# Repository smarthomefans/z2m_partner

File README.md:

# [中文文档](https://bbs.iobroker.cn/t/topic/882)

# z2m hardware module

This is hardware module for [iobroker.zigbee](https://github.com/ioBroker/ioBroker.zigbee) and [zigbee2mqtt](https://github.com/Koenkk/zigbee2mqtt) or [Zigbee to Tasmota](https://github.com/arendst/Tasmota/wiki/Zigbee).  
If you can speak Chinese and be interested with this project, please look at this [post](https://bbs.iobroker.cn/t/topic/882/33) in [ioBroker China BBS](https://bbs.iobroker.cn/)

## **V2P1 version is ready to ship**

## What's the difference

- Use [E18-MS1PA1-IPX](http://www.ebyte.com/en/product-view-news.aspx?id=123) zigbee module. 20dBm power can make sure zigbee net work signal is strong.
- Add an ESP8266 module. Give you another option that can connect zigbee module though wifi-to-serial (I was using this [project](https://github.com/smarthomefans/ESP32-Serial-Bridge)).
If your machine running smarthome platform, such as ioBroker or homeassistant, is put in a hidden corner, for better signal coverage, you can put your zigbee module in some where else.
- ESP8266 connected to E18 firmware download pins, give you a chance that can update E18 though ESP8266, no need to use CC-DEBUG.
- There will be 4 options for different TTY connection:
  - USB TTY <==> ESP 8266 TTY. This option is used for download firmware for E18.
  - USB TTY <==> E18 TTY. If you can connect your module though USB wire, this is more stable.
  - USB TTY <==> ESP 8266 debug port. ESP 8266 TTY <==> E18 TTY. Connect though wifi, and you can capture debug infomation though USB TTY.
  - ESP 8266 TTY <==> E18 TTY. Connect though TTY.

## Hardware module images

## 3D cover

## [SCH](https://github.com/smarthomefans/z2m_partner/raw/master/project/z2m_partner.pdf) preview

## PCB preview

## BOM list
[BOM](https://github.com/smarthomefans/z2m_partner/blob/master/documents/bom.md) can get from here.

## Thanks to

- [modkam](https://modkam.ru/), [kirovilya](https://github.com/kirovilya), [Koenkk](https://github.com/Koenkk).

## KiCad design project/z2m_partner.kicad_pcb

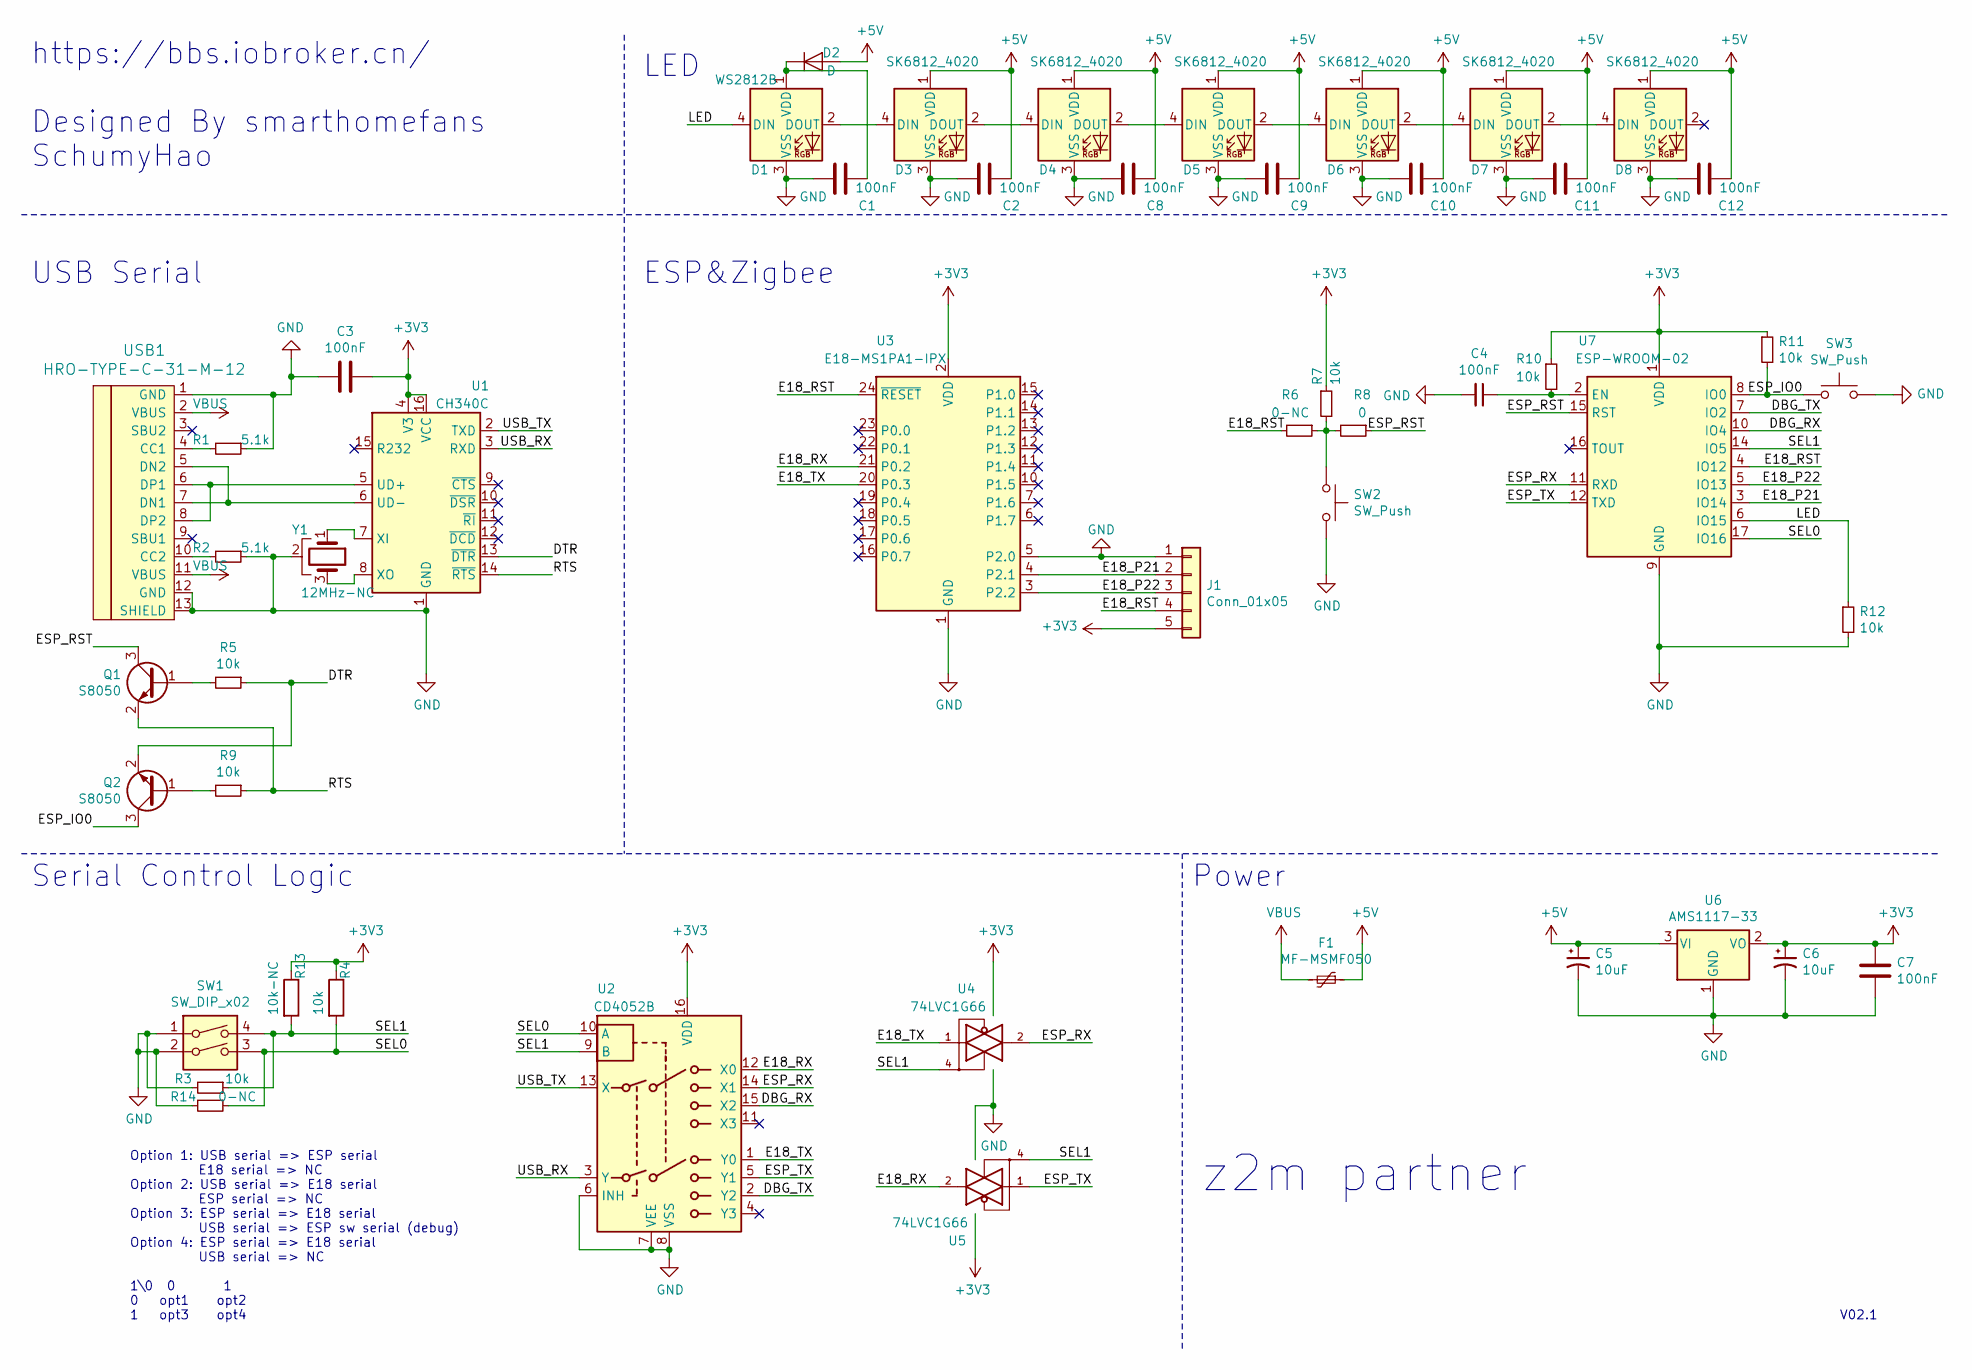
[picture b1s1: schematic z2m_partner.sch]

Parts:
C1, C2, C3, C4, C7, C8, C9, C10, C11, C12: 100nF; C_0603_1608Metric_Pad1.05x0.95mm_HandSolder
C5, C6: 10uF; CP_EIA-3528-21_Kemet-B_Pad1.50x2.35mm_HandSolder
D1: WS2812B; LED_WS2812B_PLCC4_5.0x5.0mm_P3.2mm
D2: D; D_0603_1608Metric_Pad1.05x0.95mm_HandSolder
D3, D4, D5, D6, D7, D8: SK6812_4020
F1: MF-MSMF050; Fuse_1812_4532Metric_Pad1.30x3.40mm_HandSolder
J1: Conn_01x05; PinHeader_1x05_P2.54mm_Vertical
Q1, Q2: S8050; TSOT-23
R1, R2: 5.1k; R_0603_1608Metric_Pad1.05x0.95mm_HandSolder
R3, R4, R5, R7, R9, R10, R11, R12: 10k; R_0603_1608Metric_Pad1.05x0.95mm_HandSolder
R6, R14: 0-NC; R_0402_1005Metric
R8: 0; R_0402_1005Metric
R13: 10k-NC; R_0402_1005Metric
SW1: SW_DIP_x02; SW_DIP_SPSTx02_Slide_Copal_CHS-02B_W7.62mm_P1.27mm
SW2, SW3: SW_Push; SW_SPST_PTS810
U1: CH340C; SOIC-16_3.9x9.9mm_P1.27mm
U2: CD4052B; SOIC-16_3.9x9.9mm_P1.27mm
U3: E18-MS1PA1-IPX
U4, U5: 74LVC1G66; SOT-353_SC-70-5_Handsoldering
U6: AMS1117-33; SOT-223-3_TabPin2
U7: ESP-WROOM-02; ESP-13-WROOM-02
USB1: HRO-TYPE-C-31-M-12; HRO-TYPE-C-31-M-12-HandSoldering
Y1: 12MHz-NC; Resonator_SMD_muRata_CSTxExxV-3Pin_3.0x1.1mm

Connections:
+3V3: C3.1, C6.1, C7.1, J1.5, R4.1, R7.1, R10.1, R11.1, R13.1, U1.4 (V3), U1.16 (VCC), U2.16 (VDD), U3.2 (VDD), U4.5 (VCC), U5.5 (VCC), U6.2 (VO), U7.1 (VDD)
+5V: C2.2, C5.1, C8.2, C9.2, C10.2, C11.2, C12.2, D2.2 (A), D3.1 (VDD), D4.1 (VDD), D5.1 (VDD), D6.1 (VDD), D7.1 (VDD), D8.1 (VDD), F1.1, U6.3 (VI)
/DBG_RX: U2.15 (X2), U7.10 (IO4)
/DBG_TX: U2.2 (Y2), U7.7 (IO2)
/DTR: Q2.2 (E), R5.1, U1.13 (~DTR)
/E18_P21: J1.2, U3.4 (P2.1), U7.3 (IO14)
/E18_P22: J1.3, U3.3 (P2.2), U7.5 (IO13)
/E18_RST: J1.4, R6.2, U3.24 (~RESET), U7.4 (IO12)
/E18_RX: U2.12 (X0), U3.21 (P0.2), U5.2
/E18_TX: U2.1 (Y0), U3.20 (P0.3), U4.1
/ESP_IO0: Q2.3 (C), R11.2, SW3.1, U7.8 (IO0)
/ESP_RST: Q1.3 (C), R8.1, U7.15 (RST)
/ESP_RX: U2.14 (X1), U4.2, U7.11 (RXD)
/ESP_TX: U2.5 (Y1), U5.1, U7.12 (TXD)
/LED: D1.4 (DIN), R12.1, U7.6 (IO15)
/RTS: Q1.2 (E), R9.1, U1.14 (~RTS)
/SEL0: R4.2, R14.1, SW1.3, U2.10 (A), U7.17 (IO16)
/SEL1: R3.1, R13.2, SW1.4, U2.9 (B), U4.4, U5.4, U7.14 (IO5)
/USB_RX: U1.3 (RXD), U2.3 (Y)
/USB_TX: U1.2 (TXD), U2.13 (X)
GND: C1.1, C2.1, C3.2, C4.2, C5.2, C6.2, C7.2, C8.1, C9.1, C10.1, C11.1, C12.1, D1.3 (VSS), D3.3 (VSS), D4.3 (VSS), D5.3 (VSS), D6.3 (VSS), D7.3 (VSS), D8.3 (VSS), J1.1, R1.1, R2.1, R3.2, R12.2, R14.2, SW1.1, SW1.2, SW2.2, SW3.2, U1.1 (GND), U2.6 (INH), U2.7 (VEE), U2.8 (VSS), U3.1 (GND), U3.5 (P2.0), U4.3 (GND), U5.3 (GND), U6.1 (GND), U7.9 (GND), U7.13 (GND), U7.18 (GND), U7.19 (GND), USB1.1 (GND), USB1.12 (GND), USB1.13 (SHIELD), Y1.2
unnamed: C1.2, D1.1 (VDD), D2.1 (K)
unnamed: C4.1, R10.2, U7.2 (EN)
unnamed: D1.2 (DOUT), D3.4 (DIN)
unnamed: D3.2 (DOUT), D4.4 (DIN)
unnamed: D4.2 (DOUT), D5.4 (DIN)
unnamed: D5.2 (DOUT), D6.4 (DIN)
unnamed: D6.2 (DOUT), D7.4 (DIN)
unnamed: D7.2 (DOUT), D8.4 (DIN)
unnamed: Q1.1 (B), R5.2
unnamed: Q2.1 (B), R9.2
unnamed: R1.2, USB1.4 (CC1)
unnamed: R2.2, USB1.10 (CC2)
unnamed: R6.1, R7.2, R8.2, SW2.1
unnamed: U1.5 (UD+), USB1.6 (DP1), USB1.8 (DP2)
unnamed: U1.6 (UD-), USB1.5 (DN2), USB1.7 (DN1)
unnamed: U1.7 (XI), Y1.1
unnamed: U1.8 (XO), Y1.3
VBUS: F1.2, USB1.2 (VBUS), USB1.11 (VBUS)

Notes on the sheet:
Option 1: USB serial => ESP serial E18 serial => NC Option 2: USB serial => E18 serial ESP serial => NC Option 3: ESP serial => E18 serial USB serial => ESP sw serial (debug) Option 4: ESP serial => E18 serial USB serial => NC 1\0 0 1 0 opt1 opt2 1 opt3 opt4
Serial Control Logic
Power
USB Serial
z2m partner
https://bbs.iobroker.cn/ Designed By smarthomefans SchumyHao
ESP&Zigbee
V02.1
LED

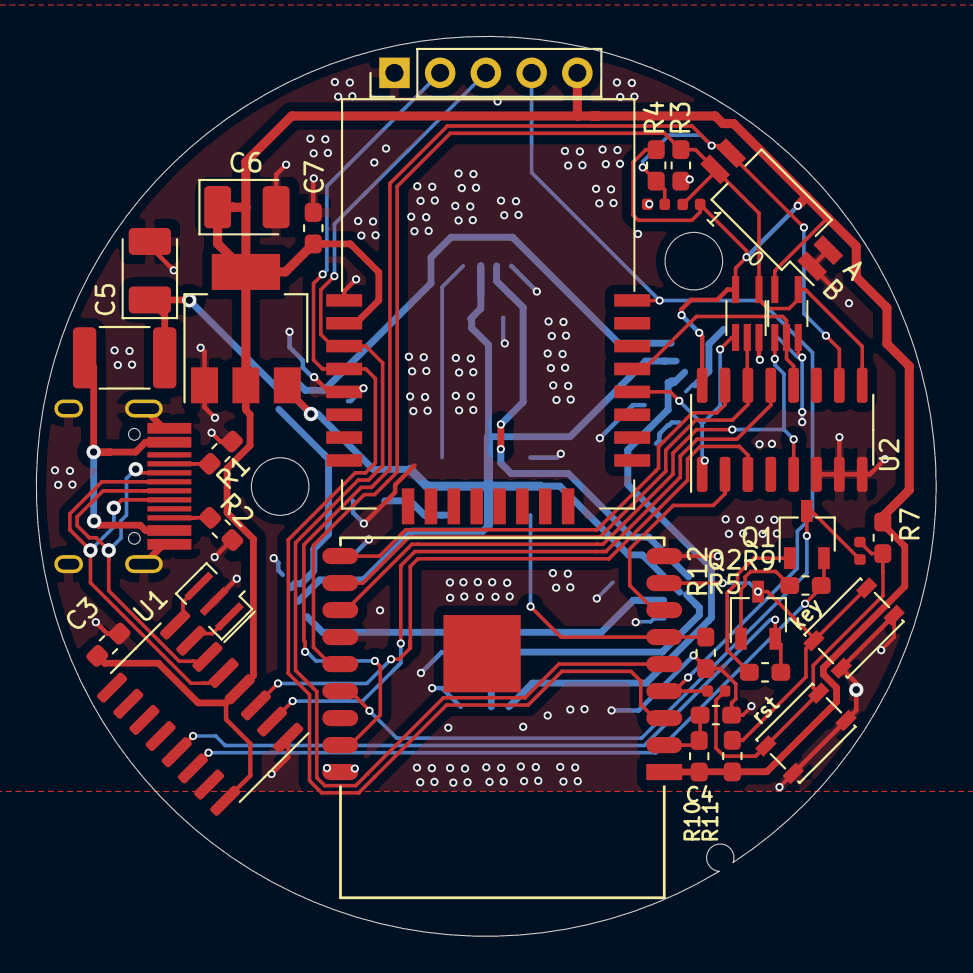
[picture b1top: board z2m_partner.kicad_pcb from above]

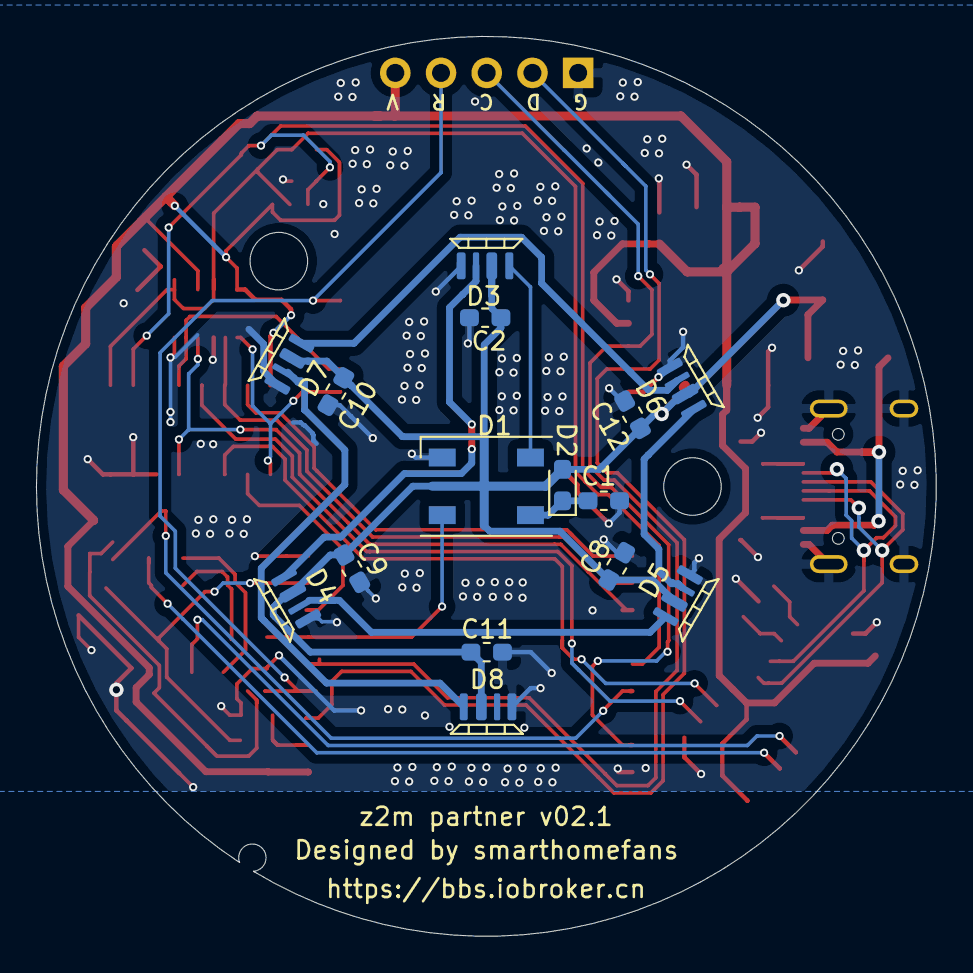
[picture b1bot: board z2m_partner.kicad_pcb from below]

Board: 2 copper layers, 50.0 x 50.0 mm, 50 parts (15 on the bottom side), 39 nets.

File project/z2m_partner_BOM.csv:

"Comment","Description","Designator","Footprint","LibRef","Pins","Quantity","PartNumber","url",
"100nF","desc","C3,C4,C7,","C_0603_1608Metric_Pad1.05x0.95mm_HandSolder","libref","2","3","","~",
"10uF","desc","C5,C6,","CP_EIA-3528-21_Kemet-B_Pad1.50x2.35mm_HandSolder","libref","2","2","","~",
"MF-MSMF050","desc","F1,","Fuse_1812_4532Metric_Pad1.30x3.40mm_HandSolder","libref","2","1","","~",
"S8050","desc","Q1,Q2,","TSOT-23","libref","3","2","","~",
"5.1k","desc","R1,R2,","R_0603_1608Metric_Pad1.05x0.95mm_HandSolder","libref","2","2","","~",
"10k-NC","desc","R13,","R_0402_1005Metric","libref","2","1","","~",
"10k","desc","R4,R7,R10,R11,R12,R5,R9,R3,","R_0603_1608Metric_Pad1.05x0.95mm_HandSolder","libref","2","8","","~",
"0-NC","desc","R6,R14,","R_0402_1005Metric","libref","2","2","","~",
"0","desc","R8,","R_0402_1005Metric","libref","2","1","","~",
"SW_DIP_x02","desc","SW1,","SW_DIP_SPSTx02_Slide_Copal_CHS-02B_W7.62mm_P1.27mm","libref","4","1","","~",
"SW_Push","desc","SW2,SW3,","SW_SPST_PTS810","libref","4","2","","~",
"CH340C","desc","U1,","SOIC-16_3.9x9.9mm_P1.27mm","libref","16","1","","http://www.datasheet5.com/pdf-local-2195953",
"CD4052B","desc","U2,","SOIC-16_3.9x9.9mm_P1.27mm","libref","16","1","","http://www.ti.com/lit/ds/symlink/cd4052b.pdf",
"E18-MS1PA1-IPX","desc","U3,","E18-MS1PA1-IPX","libref","24","1","","http://www.cdebyte.com/en/downpdf.aspx?id=122",
"74LVC1G66","desc","U4,U5,","SOT-353_SC-70-5_Handsoldering","libref","5","2","","http://www.ti.com/lit/sg/scyt129e/scyt129e.pdf",
"AMS1117-33","desc","U6,","SOT-223-3_TabPin2","libref","4","1","","http://www.diodes.com/datasheets/AP1117.pdf",
"ESP-WROOM-02","desc","U7,","ESP-13-WROOM-02","libref","19","1","","https://www.espressif.com/sites/default/files/documentation/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",
"12MHz-NC","desc","Y1,","Resonator_SMD_muRata_CSTxExxV-3Pin_3.0x1.1mm","libref","3","1","","~",
"100nF","desc","C1,C2,C8,C9,C10,C11,C12,","C_0603_1608Metric_Pad1.05x0.95mm_HandSolder","libref","2","7","","~",
"WS2812B","desc","D1,","LED_WS2812B_PLCC4_5.0x5.0mm_P3.2mm","libref","4","1","","https://cdn-shop.adafruit.com/datasheets/WS2812B.pdf",
"D","desc","D2,","D_0603_1608Metric_Pad1.05x0.95mm_HandSolder","libref","2","1","","~",
"SK6812_4020","desc","D3,D4,D5,D6,D7,D8,","SK6812_4020","libref","4","6","","https://cdn-shop.adafruit.com/datasheets/WS2812B.pdf",
"Through Hole Items ",
"Conn_01x05","desc","J1,","PinHeader_1x05_P2.54mm_Vertical","libref","5","1","","~",
"MountingHole_3.2mm_M3_ISO14580","desc","REF**,REF**,","MountingHole_3.2mm_M3_ISO14580","libref","1","2","","",
"HRO-TYPE-C-31-M-12","desc","USB1,","HRO-TYPE-C-31-M-12-HandSoldering","libref","18","1","","",

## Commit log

2019-10-27 sch first version
2019-10-27 assign footprints
2019-10-27 Update e18 footprint
2019-10-27 layout finish
2019-10-28 Update silk
2019-10-28 add guide
2019-10-28 Add gerber files
2019-10-30 Add image
2019-10-30 Add licenses
2019-11-03 Add hardware images
2019-11-09 Move kicad project to folder
2019-11-09 Add 3D cover
2019-11-09 Update doc
2019-11-09 Add signal image
2019-11-09 Add signal
2019-11-09 add sponsor
2019-11-11 Create sponsor
2019-11-11 Rename sponsor to sponsor.md
2019-11-18 Update to v02
2019-11-18 Add rgb led datasheet
2019-11-19 update file structure
2019-11-20 Add esp firmware source code
2019-11-20 Enable debug
2019-11-24 Add v01 3d cover
2019-11-24 check spiffs mount status
2019-11-24 add default config
2019-11-24 Add firmware bin
2019-11-24 Fix spiffs mount issue
2019-11-24 Update RM
2019-11-24 Add tty config
2019-12-03 remove old geber
2019-12-03 set select pin in code
2019-12-03 update esp bin
2019-12-03 remove unused files
2019-12-03 remove port config
2019-12-03 Bump ser2net version to 0.0.5
2019-12-04 Bump ser2net fw version to 0.0.6
2019-12-15 add 8050 datasheet
2019-12-15 add gitignore
2019-12-15 update esp fw
2019-12-16 fix pdf
2019-12-16 update bom
2019-12-17 fix sel pin-mode
2019-12-20 修复中文文档连接
2020-01-08 Add v2p1 3D cave
2020-03-19 Add new esp firmware
2020-03-24 Add OTA zigbee fw
2020-03-24 remove module from framework
2020-04-03 Add OTP firmware
2020-05-25 Add z2mp Tasmota sub module
2020-05-25 Add tasmota images
2021-11-10 Update README_zh.md
    https://forum.kicad.info/t/warning-avoid-all-links-to-kicad-pcb-org-use-kicad-org/31521
